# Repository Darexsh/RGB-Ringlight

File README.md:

* * *

<div align="center">

🌈 RGB Ringlight – LED Chaser
============================

**🟥🟩🟦 RGB LED Chaser using 3 mm LEDs**  

Powered by NE555, CD4017, and a speed control potentiometer

<sub>Check out my bot in Telegram for an easy project overview.<br>If you want to support more projects, you can leave a small donation for a coffee.</sub>

</div>

* * *

✨ Authors
---------

| Name | GitHub | Role | Contact | Contributions |
| --- | --- | --- | --- | --- |
| **[Darexsh by Daniel Sichler](https://github.com/Darexsh)** | [Link](https://github.com/Darexsh?tab=repositories) | Hardware & Schematic 🖥️🛠️| 📧 [E-Mail](mailto:sichler.daniel@gmail.com) | Concept, Layout, Integration |

* * *

🚀 About the Project
--------------------

This project is an **RGB ring light with a chaser animation**, built entirely from discrete electronics.
The core consists of:
* **NE555:** Clock Generator
* **CD4017:** Decade Counter
* **24 LEDs:** Positioned in Circle shape with with alternatingly positioned red, green and blue LEDs
    
The **chase speed** can be adjusted using a **10 kΩ potentiometer**.
Power is supplied through a **9 V barrel jack (5.5 mm)**.

* * *

🛠️ How It Works
===========

🔁 **Main Function**
* The **NE555** operates in astable mode, generating a variable clock signal.
* The **CD4017** advances one output pin per clock pulse.
* Each LED lights up sequentially → creating the classic **LED chaser effect**.

💡 **LED Layout**

The ring contains **24 LEDs** total:
* 🔴 **D1–D8:** Red
* 🟢 **D9–D16:** Green
* 🔵 **D17–D24:** Blue

🎚️ **Speed Control**
* A **10 kΩ potentiometer (RV1)** adjusts the NE555 frequency.

🔌 **Power Supply**
* **9 V DC input**
* Supplied through a **5.5 mm barrel jack**

* * *

📋 Bill of Materials (BOM)
===========

| Part       | Value / Type                              |
| ---------- | ----------------------------------------- |
| **IC1**    | CD4017BE                                  |
| **IC2**    | NE555P                                    |
| **LEDs**   | 24× 3 mm LEDs (8× red, 8× green, 8× blue) |
| **R1–R24** | 680 Ω                                     |
| **R25**    | 10 kΩ                                     |
| **RV1**    | 10 kΩ potentiometer                       |
| **C1**     | 10 µF / 25 V                              |
| **J1**     | DC barrel jack 5.5 mm (with switch)       |
| **J2**     | Socket for CD4017                         |
| **J3**     | Socket for NE555                          |
| **H1**     | Mounting hole                             |

* * *

## 📜 License

This project is licensed under the **MIT License**.

This license applies to the updater application code in this repository. Upstream patch and app projects remain under their own licenses and notice terms.

**Copyright (c) 2026 Darexsh by Daniel Sichler**

You are free to use, copy, modify, merge, publish, distribute, sublicense, and sell this software under the terms of the MIT License.

When redistributing this project, you must include the original copyright notice and the MIT License permission notice.

**Developer:** Darexsh by Daniel Sichler.

The full license is available in the [LICENSE](LICENSE) file.

* * *

<!-- Keep this line! Rendered picture of PCB is going to be displayed after Production files are pushed to branch! -->

<div align="center"> <sub>Created with ❤️ by Daniel Sichler</sub> </div>

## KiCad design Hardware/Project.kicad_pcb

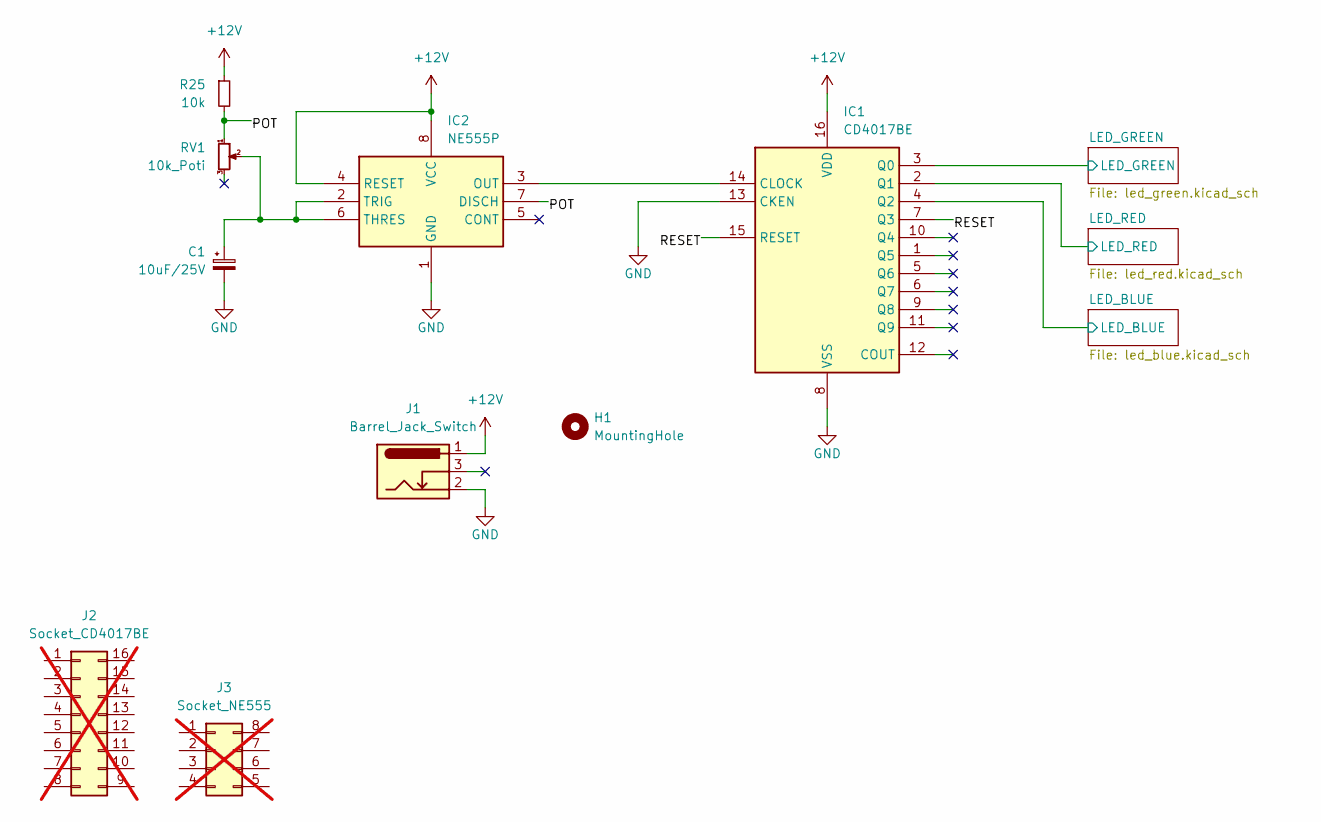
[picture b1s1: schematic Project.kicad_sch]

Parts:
C1: 10uF/25V; CP_Radial_D4.0mm_P2.00mm; LCSC C43347
H1: MountingHole; MountingHole_3.2mm_M3
IC1: CD4017BE; LCSC C51898328
IC2: NE555P; LCSC C51927330
J1: Barrel_Jack_Switch; BarrelJack_Horizontal; LCSC C3096082
J2: Socket_CD4017BE; LCSC C2326; not fitted
J3: Socket_NE555; LCSC C72124; not fitted
R25: 10k; R_Axial_DIN0204_L3.6mm_D1.6mm_P7.62mm_Horizontal; LCSC C2903232
RV1: 10k_Poti; Potentiometer_Runtron_RM-065_Vertical; LCSC C5205021

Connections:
+12V: IC1.16 (VDD), IC2.4 (RESET), IC2.8 (VCC), J1.1, R25.1
/LED_BLUE/LED_BLUE: IC1.4 (Q2); also elsewhere on the board
/LED_GREEN/LED_GREEN: IC1.3 (Q0); also elsewhere on the board
/LED_RED/LED_RED: IC1.2 (Q1); also elsewhere on the board
/POT: IC2.7 (DISCH), R25.2, RV1.1
/RESET: IC1.7 (Q3), IC1.15 (RESET)
GND: C1.2, IC1.8 (VSS), IC1.13 (CKEN), IC2.1 (GND), J1.2; also elsewhere on the board
unnamed: IC1.14 (CLOCK), IC2.3 (OUT)
unnamed: C1.1, IC2.2 (TRIG), IC2.6 (THRES), RV1.2

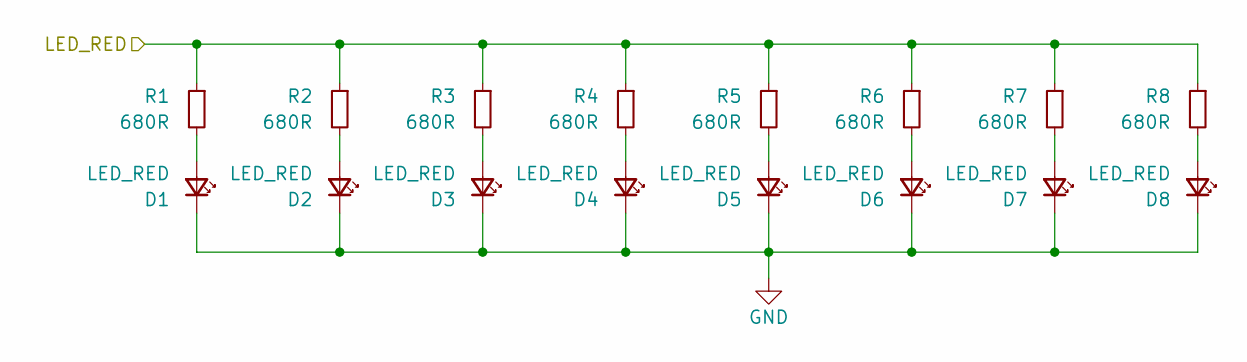
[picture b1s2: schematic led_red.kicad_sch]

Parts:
D1, D2, D3, D4, D5, D6, D7, D8: LED_RED; LED_D3.0mm; LCSC C2895470
R1, R2, R3, R4, R5, R6, R7, R8: 680R; R_0603_1608Metric

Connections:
/LED_RED/LED_RED: R1.1, R2.1, R3.1, R4.1, R5.1, R6.1, R7.1, R8.1; also elsewhere on the board
GND: D1.1 (K), D2.1 (K), D3.1 (K), D4.1 (K), D5.1 (K), D6.1 (K), D7.1 (K), D8.1 (K); also elsewhere on the board
unnamed: D1.2 (A), R1.2
unnamed: D2.2 (A), R2.2
unnamed: D3.2 (A), R3.2
unnamed: D4.2 (A), R4.2
unnamed: D5.2 (A), R5.2
unnamed: D6.2 (A), R6.2
unnamed: D7.2 (A), R7.2
unnamed: D8.2 (A), R8.2

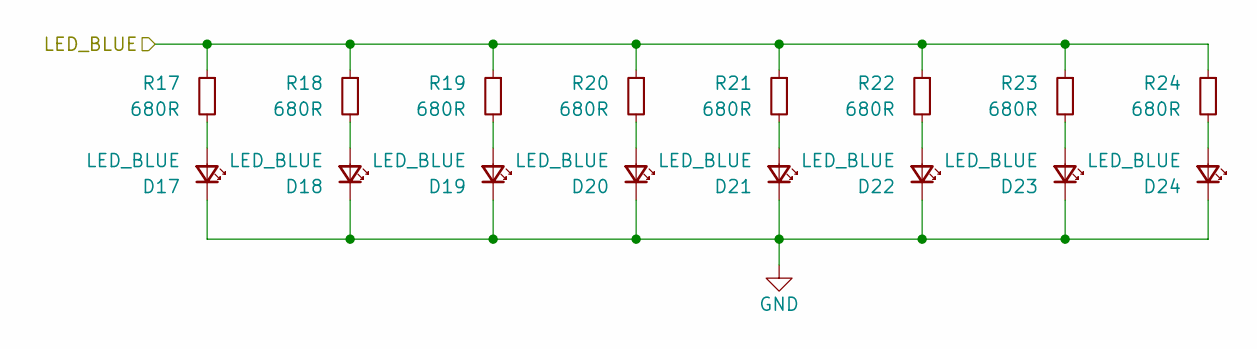
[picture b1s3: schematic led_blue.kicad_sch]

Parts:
D17, D18, D19, D20, D21, D22, D23, D24: LED_BLUE; LED_D3.0mm; LCSC C2895474
R17, R18, R19, R20, R21, R22, R23, R24: 680R; R_0603_1608Metric

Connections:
/LED_BLUE/LED_BLUE: R17.1, R18.1, R19.1, R20.1, R21.1, R22.1, R23.1, R24.1; also elsewhere on the board
GND: D17.1 (K), D18.1 (K), D19.1 (K), D20.1 (K), D21.1 (K), D22.1 (K), D23.1 (K), D24.1 (K); also elsewhere on the board
unnamed: D17.2 (A), R17.2
unnamed: D18.2 (A), R18.2
unnamed: D19.2 (A), R19.2
unnamed: D20.2 (A), R20.2
unnamed: D21.2 (A), R21.2
unnamed: D22.2 (A), R22.2
unnamed: D23.2 (A), R23.2
unnamed: D24.2 (A), R24.2

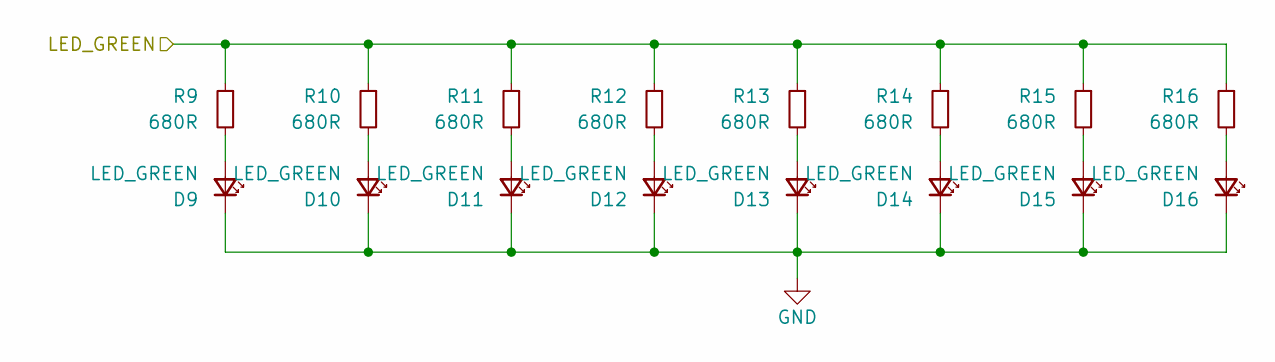
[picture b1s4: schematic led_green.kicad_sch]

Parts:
D9, D10, D11, D12, D13, D14, D15, D16: LED_GREEN; LED_D3.0mm; LCSC C7470728
R9, R10, R11, R12, R13, R14, R15, R16: 680R; R_0603_1608Metric

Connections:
/LED_GREEN/LED_GREEN: R9.1, R10.1, R11.1, R12.1, R13.1, R14.1, R15.1, R16.1; also elsewhere on the board
GND: D9.1 (K), D10.1 (K), D11.1 (K), D12.1 (K), D13.1 (K), D14.1 (K), D15.1 (K), D16.1 (K); also elsewhere on the board
unnamed: D9.2 (A), R9.2
unnamed: D10.2 (A), R10.2
unnamed: D11.2 (A), R11.2
unnamed: D12.2 (A), R12.2
unnamed: D13.2 (A), R13.2
unnamed: D14.2 (A), R14.2
unnamed: D15.2 (A), R15.2
unnamed: D16.2 (A), R16.2

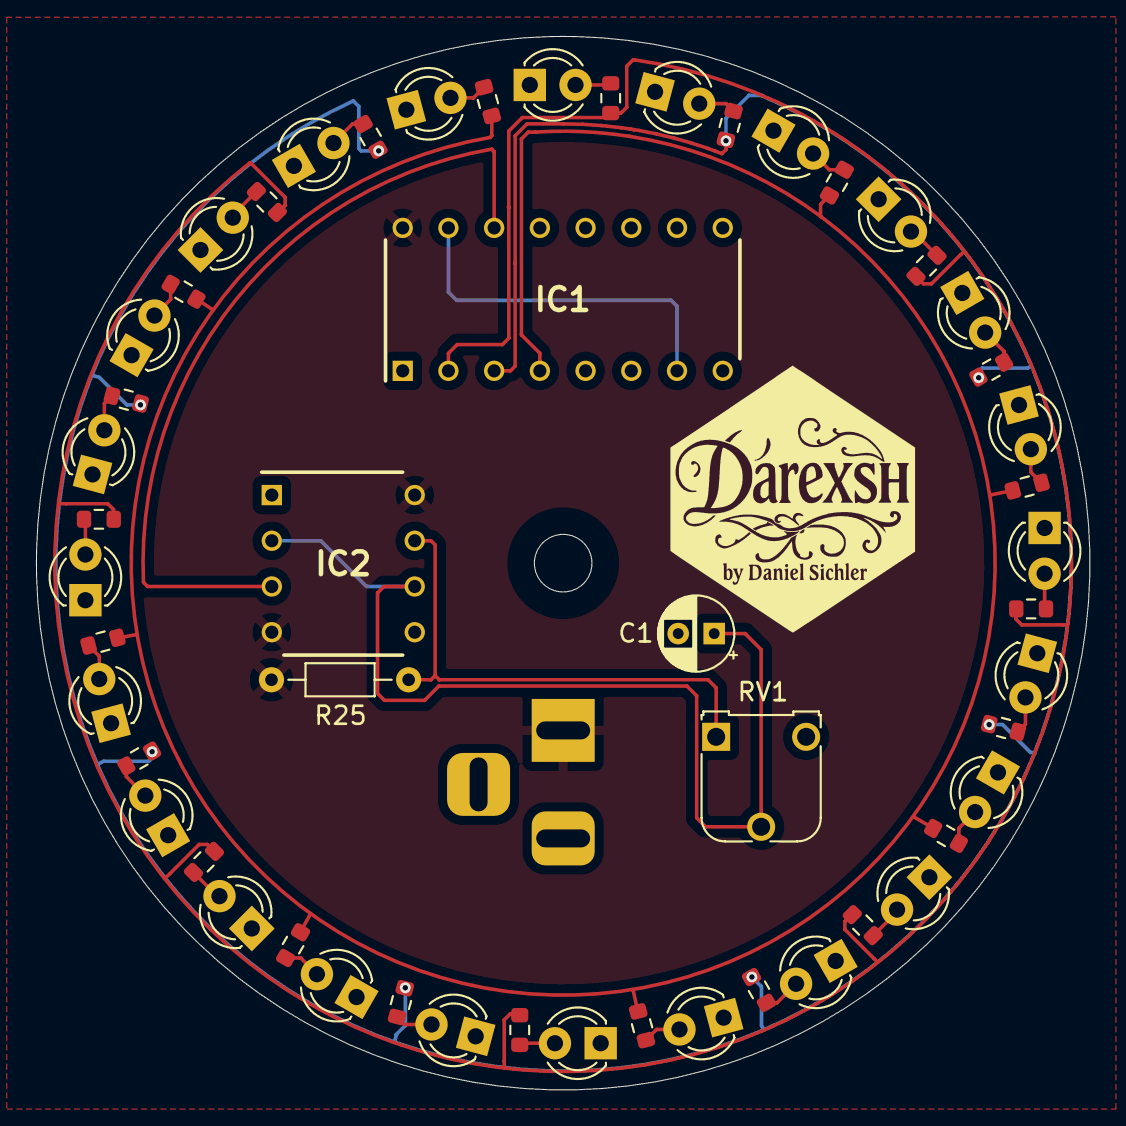
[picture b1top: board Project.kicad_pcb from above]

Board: 2 copper layers, 58.5 x 58.5 mm, 55 parts (1 on the bottom side), 33 nets.

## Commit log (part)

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2025-12-12 Added Ringlight
2025-12-12 Changed README
2025-12-12 Rendered pictures are now shown
2025-12-12 Added first PCB without series resistor
2025-12-12 Correct appearances in 3D viewer and rendered pictures
2026-01-29 Revise license and badge text in README
    Updated license information and badge labels in README.md.
2026-01-29 Revise non-commercial license terms and conditions
2026-01-29 Add 'Buy Me a Coffee' badge to README
    Added a 'Buy Me a Coffee' badge to the README.
2026-01-29 Update contributor name format in README
2026-03-18 Enhance README with Telegram bot and donation links
